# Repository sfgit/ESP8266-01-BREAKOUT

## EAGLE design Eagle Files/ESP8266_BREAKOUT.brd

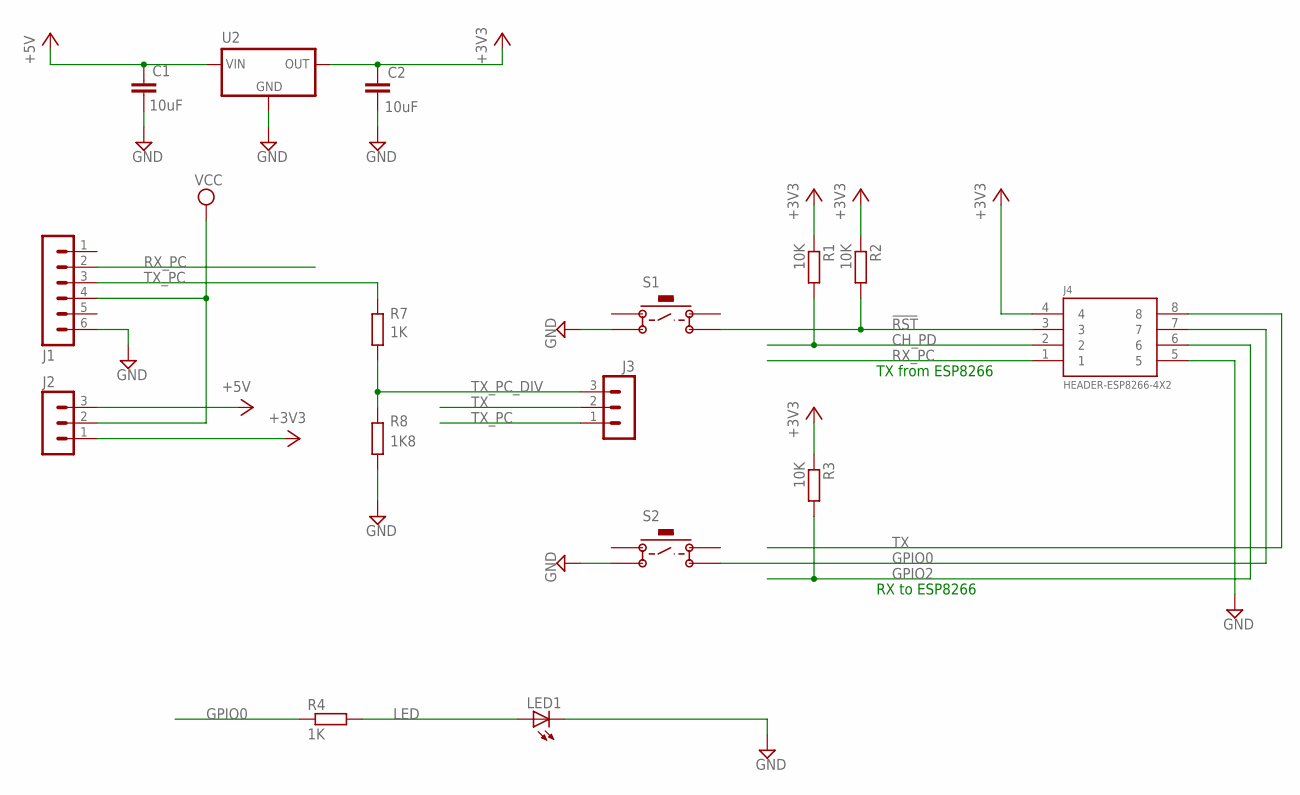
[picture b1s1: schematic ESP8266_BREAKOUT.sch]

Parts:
C1, C2: 10uF; C5B2.5
J1: MA06-1
J2, J3: MA03-1
J4: HEADER-ESP8266-4X2; HEADER-4X2-A
LED1: LED5MM
R1, R2, R3: 10K; 0204/7
R4, R7: 1K; 0204/7
R8: 1K8; 0204/7
S1, S2: 1825910-6-SPST-NOPB-4P; SW-NOPB-4
U2: LM1117-3V3-T0-220; TO-220

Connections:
!RST: J4.3, R2.2, S1.4
+3V3: C2.2, J2.1, J4.4, R1.1, R2.1, R3.1, U2.P$2 (OUT)
+5V: C1.2, J2.3, U2.P$3 (IN)
CH_PD: J4.2, R1.2
GND: C1.1, C2.1, J1.6, J4.5, LED1.K (C), R8.1, S1.2, S2.2, U2.P$1 (GND)
GPIO0: J4.7, R4.1, S2.4
GPIO2: J4.6, R3.2
LED: LED1.A, R4.2
RX_PC: J1.2, J4.1
TX: J3.2, J4.8
TX_PC: J1.3, J3.1, R7.2
TX_PC_DIV: J3.3, R7.1, R8.2
VCC: J1.4, J2.2

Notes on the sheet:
TX from ESP8266
RX to ESP8266

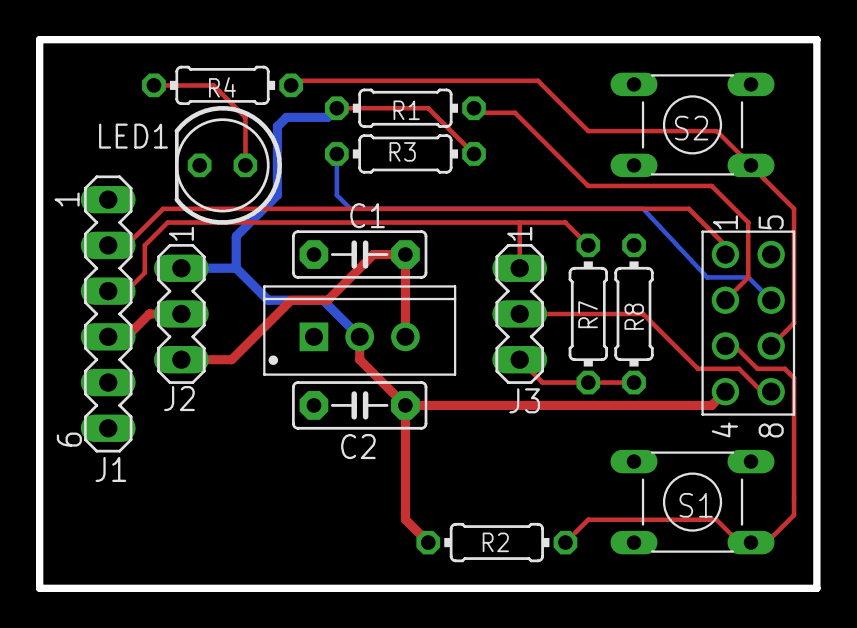
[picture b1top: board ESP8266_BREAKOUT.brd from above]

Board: 2 copper layers, 43.2 x 30.5 mm, 16 parts (0 on the bottom side), 13 nets.

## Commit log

2015-05-11 Uploading Source Files
    Uploading altium source files and some additional lua files.
2015-05-11 Uploading PDF Sch PCB BOM
    Uploading a PDF copy of the complete schematics, PCB, and simplified BOM
    files
2015-05-12 Uploading Eagle Files
    Uploading the Eagle files from the workshop with a few small tweaks
    including the addition of a normally open pushbutton and a modified
    LM1117 (libraries included)
2015-05-25 Revert "Initial Commit"
    This reverts commit 64c9dc2e9c6b987721da5016810945d4769e944d.
2015-06-13 Update Eagle Files
2015-06-13 Uploading Fritzing File
2015-06-13 Uploading presentation
2015-06-13 Deleting duplicate folder
